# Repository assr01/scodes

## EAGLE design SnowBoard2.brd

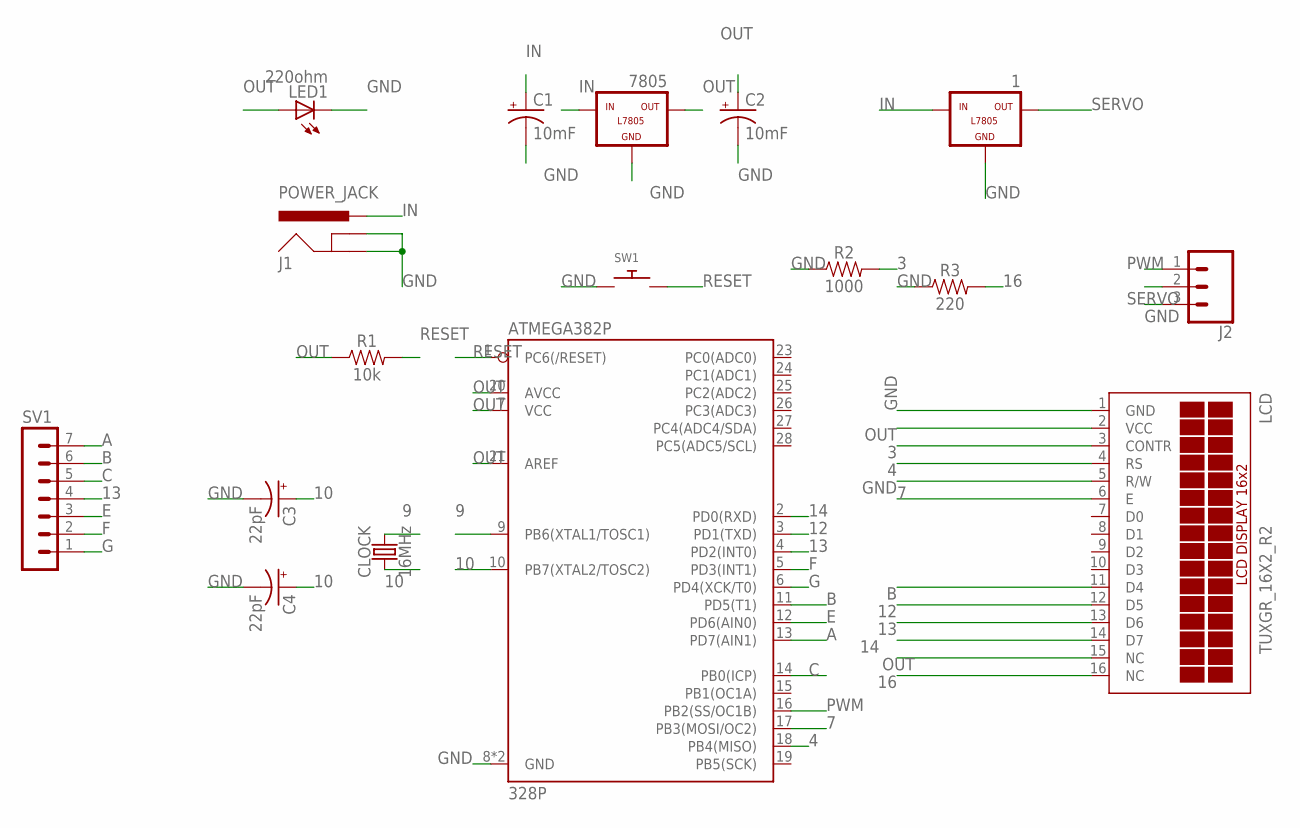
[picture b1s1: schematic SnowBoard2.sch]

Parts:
1, 7805: L7805; 78XXL
ATMEGA382P: 328P; DIP28
C1, C2: 10mF; CPOL-RADIAL-5MM-10MM
C3, C4: 22pF; CPOL-RADIAL-5MM-10MM
CLOCK: 16MHz; HC49US
J1: POWER_JACK; POWER_JACK_PTH
J2: CONN_03-SCREW-5MM; SCREWTERMINAL-5MM-3
LCD: TUXGR_16X2_R2
LED1: 220ohm; LED5MM
R1: 10k; AXIAL-0.1
R2: 1000; AXIAL-0.1-KIT
R3: 220; AXIAL-0.1-KIT
SV1: MA07-1
SW1: SWITCH_PUSHBUTTONEVQ-PE; TACT_PANA-EVQ

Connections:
3: LCD.3 (CONTR), R2.P$2 (2)
4: ATMEGA382P.18 (PB4(MISO)), LCD.4 (RS)
7: ATMEGA382P.17 (PB3(MOSI/OC2)), LCD.6 (E)
9: ATMEGA382P.9 (PB6(XTAL1/TOSC1)), CLOCK.2
10: ATMEGA382P.10 (PB7(XTAL2/TOSC2)), C3.+, C4.+, CLOCK.1
12: ATMEGA382P.3 (PD1(TXD)), LCD.12 (D5)
13: ATMEGA382P.4 (PD2(INT0)), LCD.13 (D6), SV1.4
14: ATMEGA382P.2 (PD0(RXD)), LCD.14 (D7)
16: LCD.16 (NC), R3.P$2 (2)
A: ATMEGA382P.13 (PD7(AIN1)), SV1.7
B: ATMEGA382P.11 (PD5(T1)), LCD.11 (D4), SV1.6
C: ATMEGA382P.14 (PB0(ICP)), SV1.5
E: ATMEGA382P.12 (PD6(AIN0)), SV1.3
F: ATMEGA382P.5 (PD3(INT1)), SV1.2
G: ATMEGA382P.6 (PD4(XCK/T0)), SV1.1
GND: 1.GND, 7805.GND, ATMEGA382P.8 (GND), ATMEGA382P.22 (GND), C1.-, C2.-, C3.-, C4.-, J1.GND, J1.GNDBREAK, J2.3, LCD.1 (GND), LCD.5 (R/W), LED1.K (C), R2.P$1 (1), R3.P$1 (1), SW1.P$1
IN: 1.IN, 7805.IN, C1.+, J1.PWR
OUT: 7805.OUT, ATMEGA382P.7 (VCC), ATMEGA382P.20 (AVCC), ATMEGA382P.21 (AREF), C2.+, LCD.2 (VCC), LCD.15 (NC), LED1.A, R1.P$1 (1)
PWM: ATMEGA382P.16 (PB2(SS/OC1B)), J2.1
RESET: ATMEGA382P.1 (PC6(/RESET)), R1.P$2 (2), SW1.P$2
SERVO: 1.OUT, J2.2

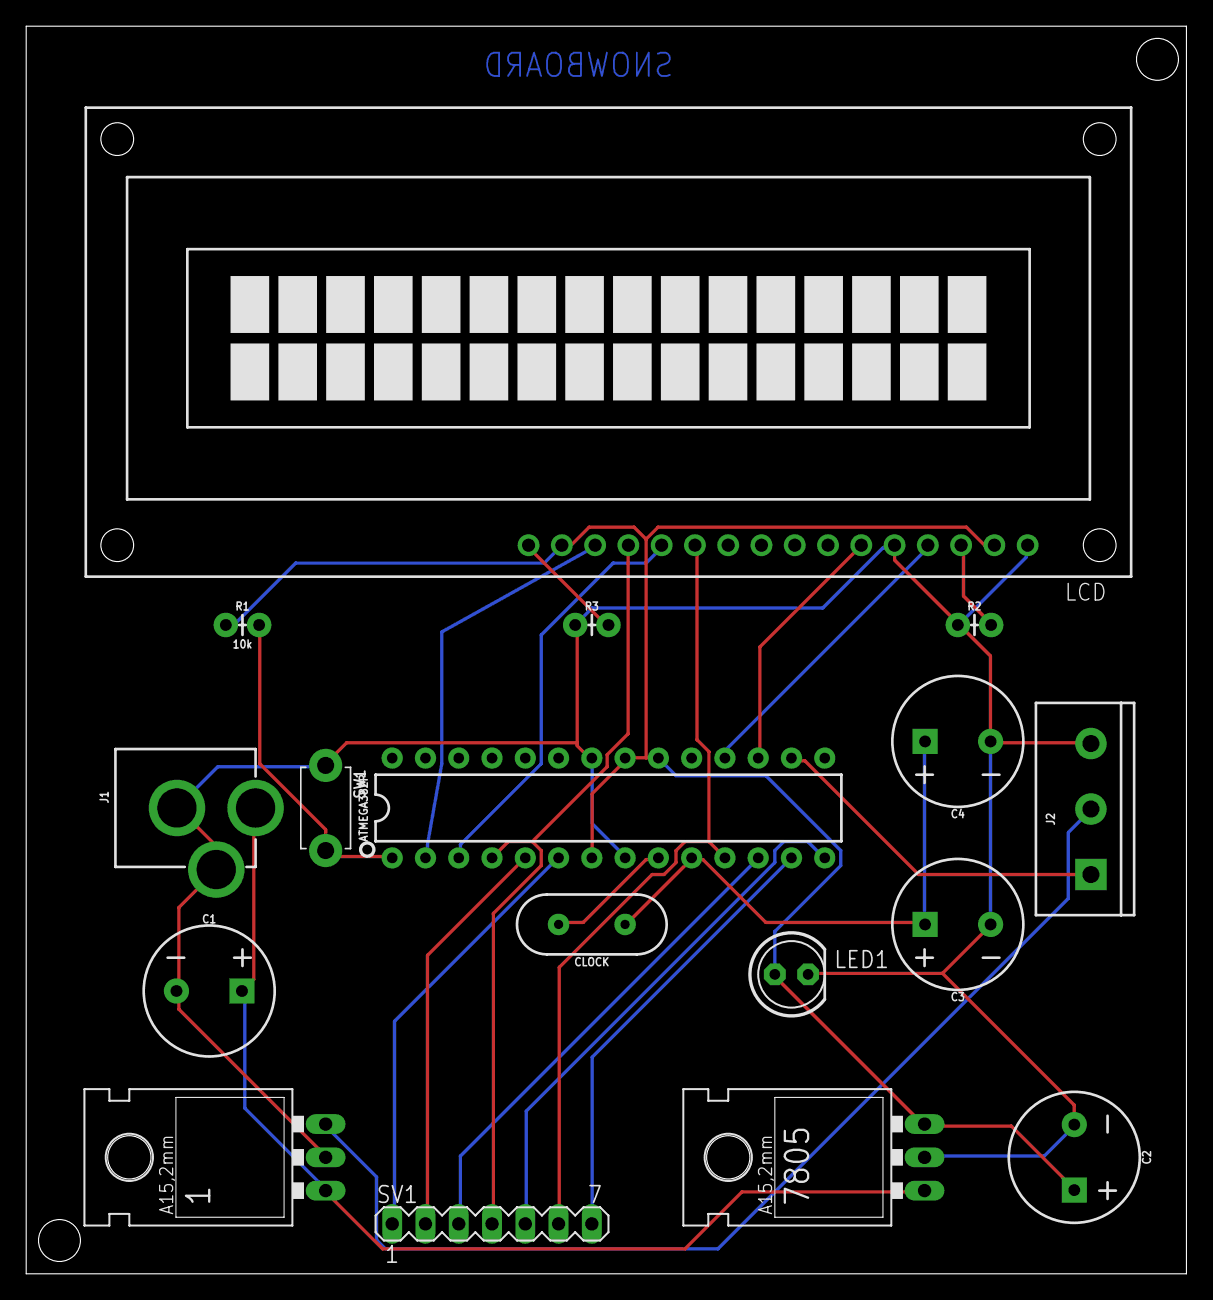
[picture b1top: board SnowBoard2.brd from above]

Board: 2 copper layers, 88.6 x 95.2 mm, 17 parts (0 on the bottom side), 21 nets.

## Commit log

2018-08-03 new files
2018-08-11 IMU MPU6050

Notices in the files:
parts and their libraries:
SparkFun-IC-Microcontroller: Licensing: Creative Commons ShareAlike 4.0 International - https://creativecommons.org/licenses/by-sa/4.0
